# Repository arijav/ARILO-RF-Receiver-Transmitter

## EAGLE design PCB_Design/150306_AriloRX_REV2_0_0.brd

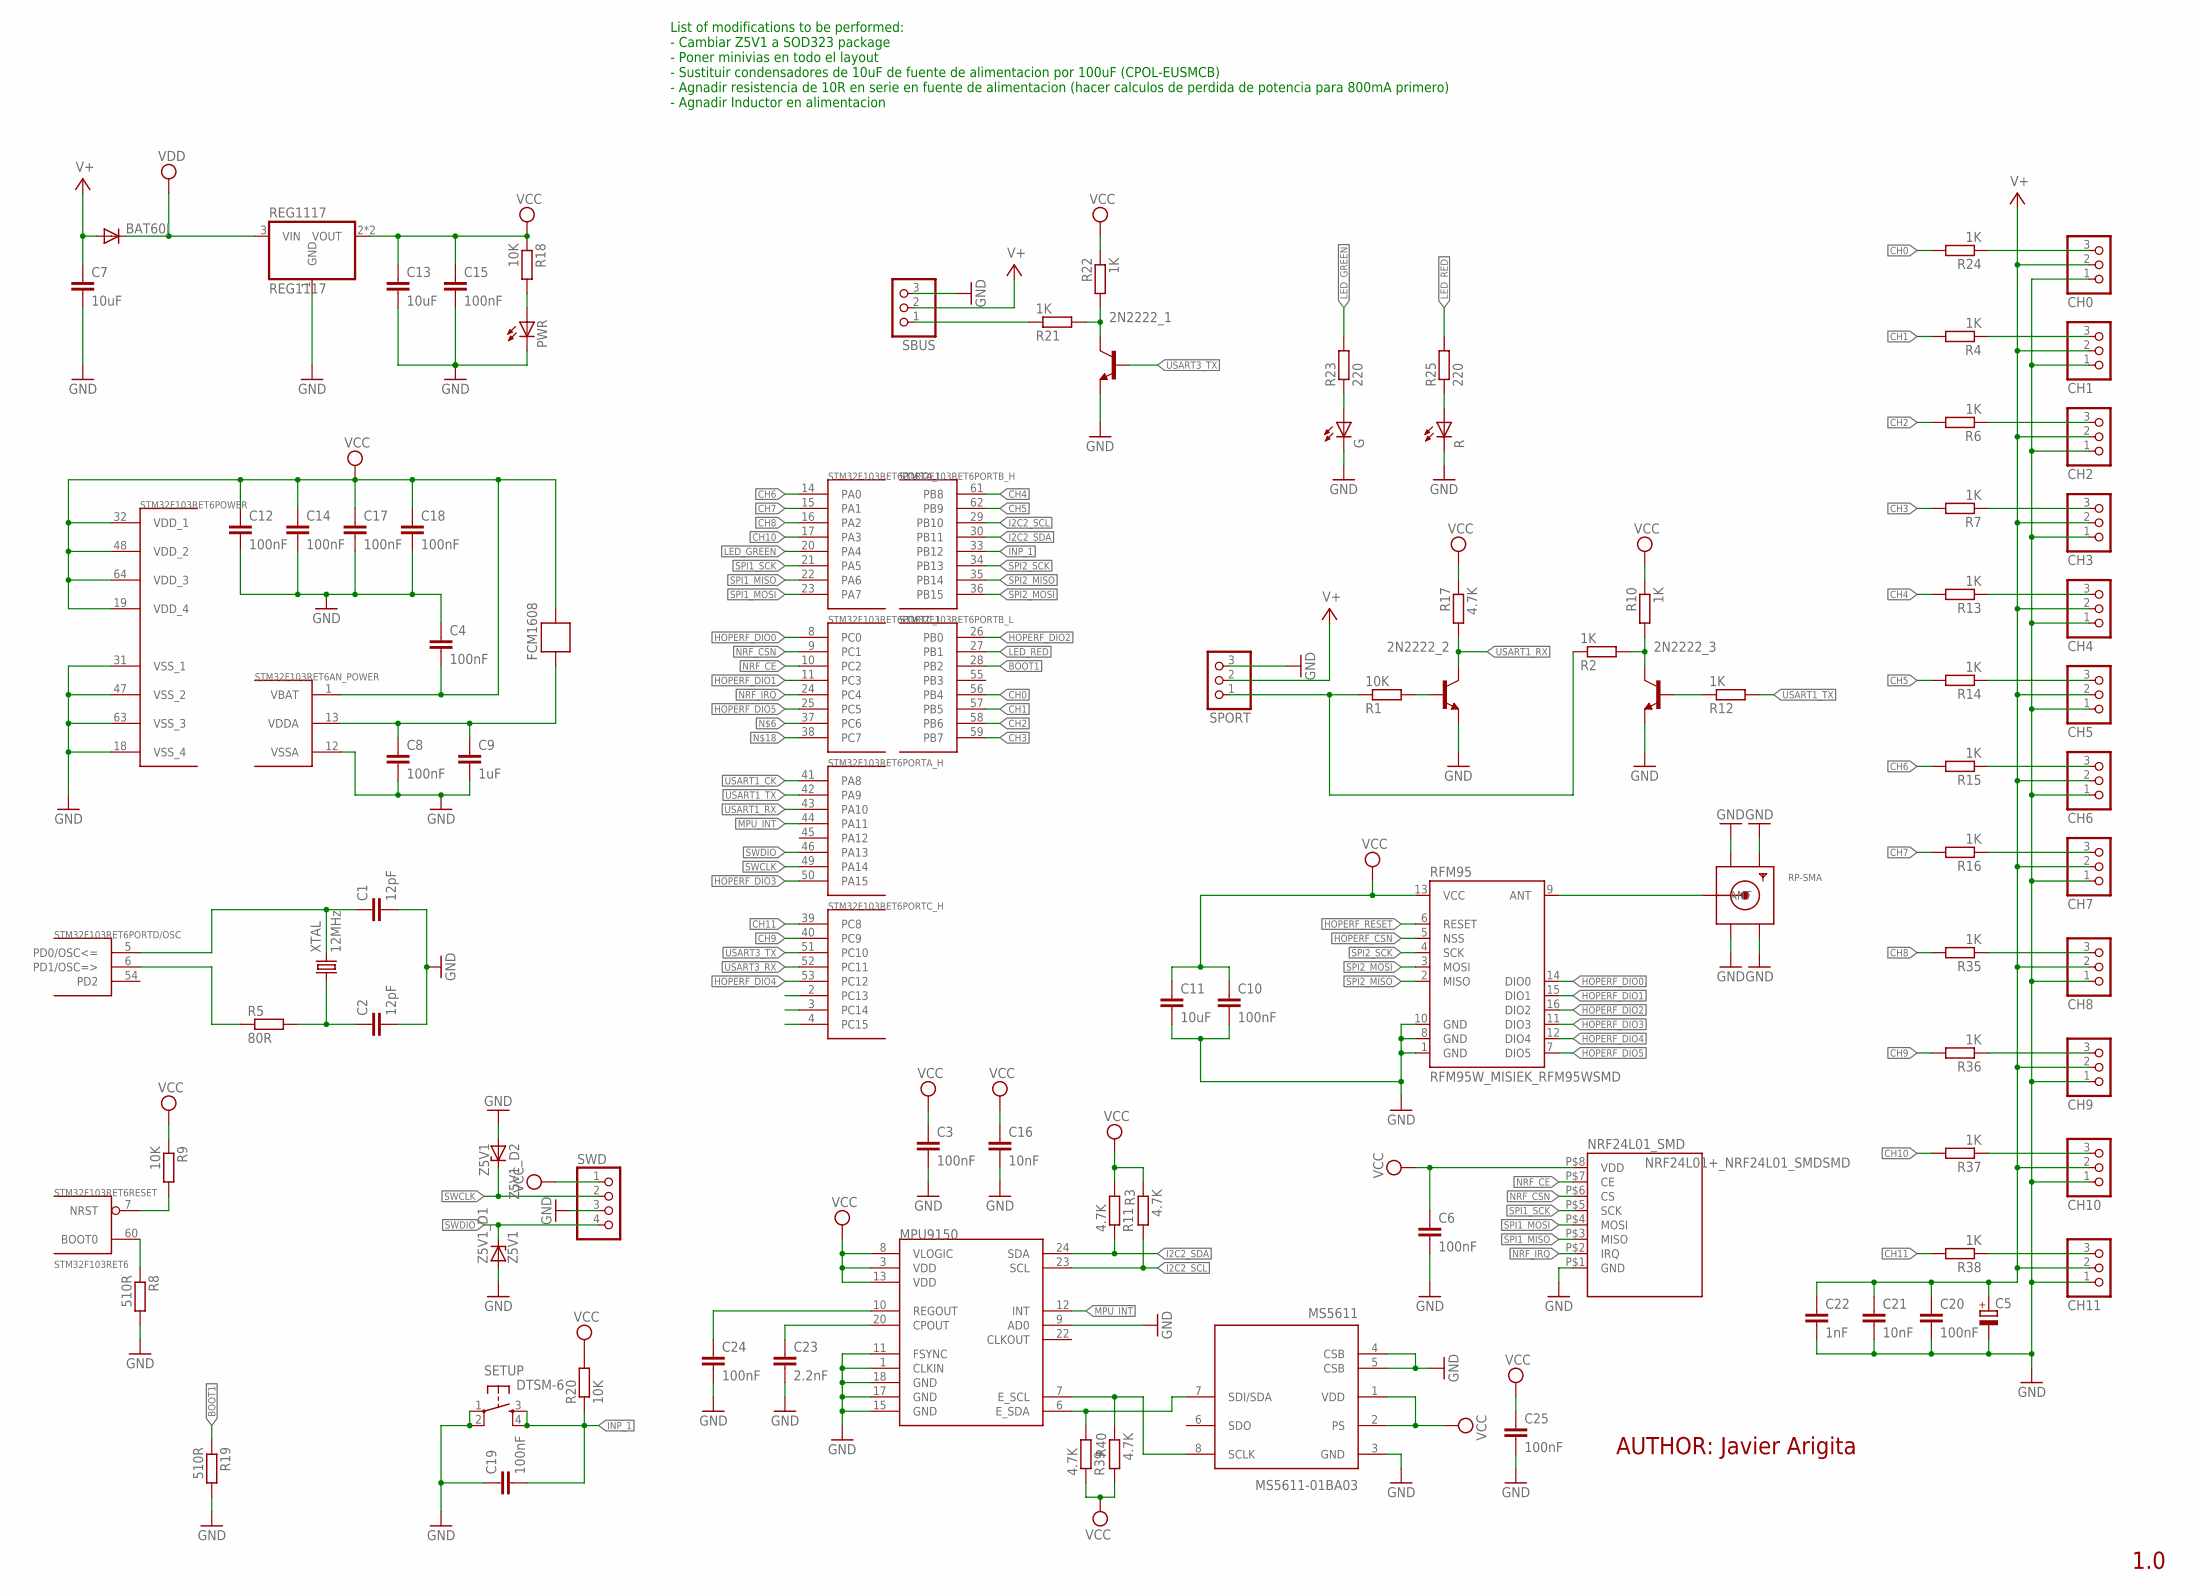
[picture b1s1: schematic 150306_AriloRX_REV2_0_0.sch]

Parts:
2N2222_1, 2N2222_2, 2N2222_3: MMBT2222ALT1-NPN-SOT23-BEC; SOT23-BEC
BAT60J: DIODE-SOD323-R; SOD323-R
C1, C2: 12pF; RESISTOR_C0603
C3, C4, C6, C8, C10, C12, C14, C15, C17, C18, C19, C20, C24, C25: 100nF; RESISTOR_C0603
C5: CPOL-EUSMCB; SMC_B
C7, C11, C13: 10uF; RESISTOR_C3216
C9: 1uF; RESISTOR_C0603
C16, C21: 10nF; RESISTOR_C0603
C22: 1nF; RESISTOR_C0603
C23: 2.2nF; RESISTOR_C0603
CH0, CH1, CH2, CH3, CH4, CH5, CH6, CH7, CH8, CH9, CH10, CH11: PINHD-1X3; 1X03
FCM1608: FERRITE-BEAD; R0603
G: LEDCHIP-LED0603; CHIP-LED0603
MPU9150: MPU-9150QFN-24-NP; QFN-24-NP
MS5611: MS5611-01BA03; SON125P300X500X100-8N
NRF24L01_SMD: NRF24L01+_NRF24L01_SMDSMD; NRF24L01+_NRF24L01_SMD
PWR: LED_LEDCHIP-LED0603; LED_CHIP-LED0603
R: LEDCHIP-LED0603; CHIP-LED0603
R1, R9, R18, R20: 10K; RCL_R0603
R2, R4, R6, R7, R10, R12, R13, R14, R15, R16, R21, R22, R24, R35, R36, R37, R38: 1K; RCL_R0603
R3, R11, R17, R39, R40: 4.7K; RCL_R0603
R5: 80R; RCL_R0603
R8, R19: 510R; RCL_R0603
R23, R25: 220; RCL_R0603
REG1117: REG1117; SOT223
RFM95: RFM95W_MISIEK_RFM95WSMD; RFM95W_MISIEK_RFM95W_SMD
RP-SMA: SMACONNECTOR_EDGE; SMA_EDGELAUNCH
SBUS: PINHD-1X3; 1X03
SETUP: DTSM-6
SPORT: PINHD-1X3; 1X03
STM32F103RET6: STM32F103RET6; TQFP64
SWD: PINHD-1X4; 1X04
XTAL: 12MHz; CRYSTAL-SMD-5X3
Z5V1_D1, Z5V1_D2: Z5V1; SOD80C

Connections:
BOOT1: R19.1, STM32F103RET6.28 (PB2)
CH0: R24.2, STM32F103RET6.56 (PB4)
CH1: R4.2, STM32F103RET6.57 (PB5)
CH2: R6.2, STM32F103RET6.58 (PB6)
CH3: R7.2, STM32F103RET6.59 (PB7)
CH4: R13.2, STM32F103RET6.61 (PB8)
CH5: R14.2, STM32F103RET6.62 (PB9)
CH6: R15.2, STM32F103RET6.14 (PA0)
CH7: R16.2, STM32F103RET6.15 (PA1)
CH8: R35.2, STM32F103RET6.16 (PA2)
CH9: R36.2, STM32F103RET6.40 (PC9)
CH10: R37.2, STM32F103RET6.17 (PA3)
CH11: R38.2, STM32F103RET6.39 (PC8)
GND: 2N2222_1.E, 2N2222_2.E, 2N2222_3.E, C1.2, C2.2, C3.2, C4.1, C5.-, C6.2, C7.2, C8.2, C9.2, C10.2, C11.2, C12.2, C13.2, C14.2, C15.2, C16.2, C17.2, C18.2, C19.1, C20.2, C21.2, C22.2, C23.2, C24.2, C25.2, CH0.1, CH1.1, CH2.1, CH3.1, CH4.1, CH5.1, CH6.1, CH7.1, CH8.1, CH9.1, CH10.1, CH11.1, G.C, MPU9150.1 (CLKIN), MPU9150.9 (AD0), MPU9150.11 (FSYNC), MPU9150.15 (GND), MPU9150.17 (GND), MPU9150.18 (GND), MS5611.3 (GND), MS5611.4 (CSB), MS5611.5 (CSB), NRF24L01_SMD.P$1 (GND), PWR.C, R.C, R8.2, R19.2, REG1117.1 (GND), RFM95.1 (GND), RFM95.8 (GND), RFM95.10 (GND), RP-SMA.GND@1 (GND4), RP-SMA.GND@2 (GND3), RP-SMA.GND@3 (GND2), RP-SMA.GND@4 (GND1), SBUS.3, SETUP.1, SETUP.2, SPORT.3, STM32F103RET6.12 (VSSA), STM32F103RET6.18 (VSS_4), STM32F103RET6.31 (VSS_1), STM32F103RET6.47 (VSS_2), STM32F103RET6.63 (VSS_3), SWD.3, Z5V1_D1.A, Z5V1_D2.A
HOPERF_CSN: RFM95.5 (NSS)
HOPERF_DIO0: RFM95.14 (DIO0), STM32F103RET6.8 (PC0)
HOPERF_DIO1: RFM95.15 (DIO1), STM32F103RET6.11 (PC3)
HOPERF_DIO2: RFM95.16 (DIO2), STM32F103RET6.26 (PB0)
HOPERF_DIO3: RFM95.11 (DIO3), STM32F103RET6.50 (PA15)
HOPERF_DIO4: RFM95.12 (DIO4), STM32F103RET6.53 (PC12)
HOPERF_DIO5: RFM95.7 (DIO5), STM32F103RET6.25 (PC5)
HOPERF_RESET: RFM95.6 (RESET)
I2C2_SCL: MPU9150.23 (SCL), R3.2, STM32F103RET6.29 (PB10)
I2C2_SDA: MPU9150.24 (SDA), R11.1, STM32F103RET6.30 (PB11)
INP_1: C19.2, R20.1, SETUP.3, SETUP.4, STM32F103RET6.33 (PB12)
LED_GREEN: R23.2, STM32F103RET6.20 (PA4)
LED_RED: R25.2, STM32F103RET6.27 (PB1)
MPU_INT: MPU9150.12 (INT), STM32F103RET6.44 (PA11)
unnamed: C1.1, STM32F103RET6.5 (PD0/OSC<=), XTAL.3 (2)
unnamed: R5.1, STM32F103RET6.6 (PD1/OSC=>)
unnamed: C2.1, R5.2, XTAL.1
unnamed: R8.1, STM32F103RET6.60 (BOOT0)
unnamed: 2N2222_3.C, R2.2, R10.2
unnamed: RFM95.9 (ANT), RP-SMA.P (ANT)
unnamed: 2N2222_3.B, R12.1
unnamed: CH0.3, R24.1
unnamed: PWR.A, R18.2
unnamed: 2N2222_1.C, R21.2, R22.2
unnamed: G.A, R23.1
unnamed: CH8.3, R35.1
unnamed: R1.1, R2.1, SPORT.1
unnamed: R.A, R25.1
unnamed: 2N2222_2.B, R1.2
unnamed: C8.1, C9.1, FCM1608.2, STM32F103RET6.13 (VDDA)
unnamed: CH2.3, R6.1
unnamed: CH4.3, R13.1
unnamed: CH9.3, R36.1
unnamed: CH10.3, R37.1
unnamed: CH11.3, R38.1
unnamed: MPU9150.7 (E_SCL), MS5611.8 (SCLK), R40.1
unnamed: MPU9150.6 (E_SDA), MS5611.7 (SDI/SDA), R39.2
unnamed: CH3.3, R7.1
unnamed: CH6.3, R15.1
unnamed: C23.1, MPU9150.20 (CPOUT)
unnamed: CH5.3, R14.1
unnamed: CH7.3, R16.1
unnamed: C24.1, MPU9150.10 (REGOUT)
unnamed: CH1.3, R4.1
NRF_CE: NRF24L01_SMD.P$7 (CE), STM32F103RET6.10 (PC2)
NRF_CSN: NRF24L01_SMD.P$6 (CS), STM32F103RET6.9 (PC1)
NRF_IRQ: NRF24L01_SMD.P$2 (IRQ), STM32F103RET6.24 (PC4)
NSRST: R9.2, STM32F103RET6.7 (NRST)
SBUS: R21.1, SBUS.1
SPI1_MISO: NRF24L01_SMD.P$3 (MISO), STM32F103RET6.22 (PA6)
SPI1_MOSI: NRF24L01_SMD.P$4 (MOSI), STM32F103RET6.23 (PA7)
SPI1_SCK: NRF24L01_SMD.P$5 (SCK), STM32F103RET6.21 (PA5)
SPI2_MISO: RFM95.2 (MISO), STM32F103RET6.35 (PB14)
SPI2_MOSI: RFM95.3 (MOSI), STM32F103RET6.36 (PB15)
SPI2_SCK: RFM95.4 (SCK), STM32F103RET6.34 (PB13)
SWCLK: STM32F103RET6.49 (PA14), SWD.2, Z5V1_D2.C
SWDIO: STM32F103RET6.46 (PA13), SWD.4, Z5V1_D1.C
USART1_CK: STM32F103RET6.41 (PA8)
USART1_RX: 2N2222_2.C, R17.2, STM32F103RET6.43 (PA10)
USART1_TX: R12.2, STM32F103RET6.42 (PA9)
USART3_RX: STM32F103RET6.52 (PC11)
USART3_TX: 2N2222_1.B, STM32F103RET6.51 (PC10)
V+: BAT60J.A, C5.+, C7.1, C20.1, C21.1, C22.1, CH0.2, CH1.2, CH2.2, CH3.2, CH4.2, CH5.2, CH6.2, CH7.2, CH8.2, CH9.2, CH10.2, CH11.2, SBUS.2, SPORT.2
VCC: C3.1, C4.2, C6.1, C10.1, C11.1, C12.1, C13.1, C14.1, C15.1, C16.1, C17.1, C18.1, C25.1, FCM1608.1, MPU9150.3 (VDD), MPU9150.8 (VLOGIC), MPU9150.13 (VDD), MS5611.1 (VDD), MS5611.2 (PS), NRF24L01_SMD.P$8 (VDD), R3.1, R9.1, R10.1, R11.2, R17.1, R18.1, R20.2, R22.1, R39.1, R40.2, REG1117.2 (VOUT), REG1117.4 (VOUT), RFM95.13 (VCC), STM32F103RET6.1 (VBAT), STM32F103RET6.19 (VDD_4), STM32F103RET6.32 (VDD_1), STM32F103RET6.48 (VDD_2), STM32F103RET6.64 (VDD_3), SWD.1
VDD: BAT60J.C, REG1117.3 (VIN)

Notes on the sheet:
AUTHOR: Javier Arigita
1.0
List of modifications to be performed: - Cambiar Z5V1 a SOD323 package - Poner minivias en todo el layout - Sustituir condensadores de 10uF de fuente de alimentacion por 100uF (CPOL-EUSMCB) - Agnadir resistencia de 10R en serie en fuente de alimentacion (hacer calculos de perdida de potencia para 8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

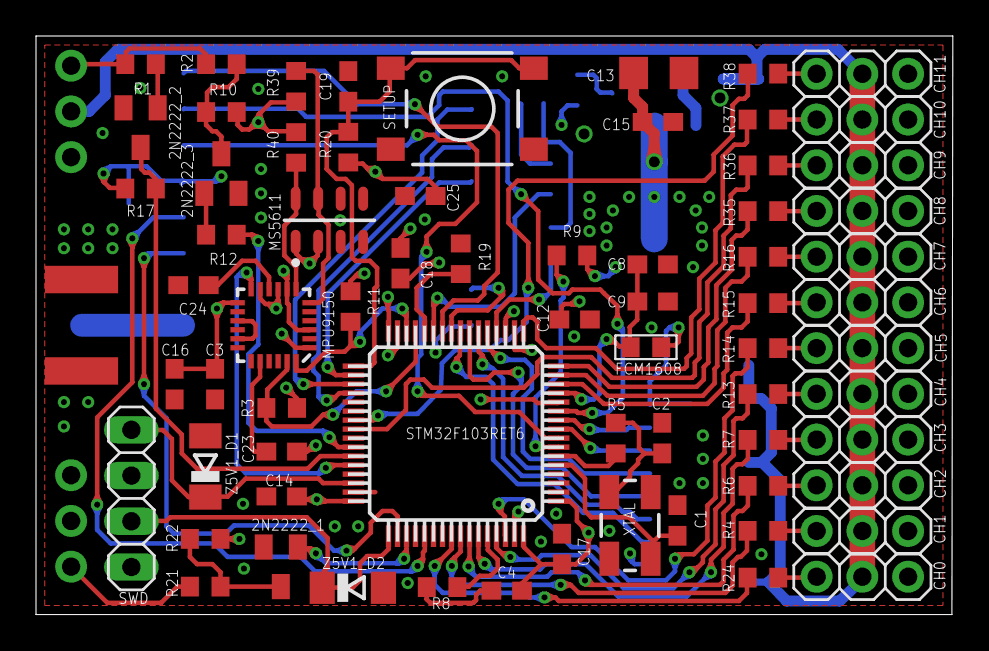
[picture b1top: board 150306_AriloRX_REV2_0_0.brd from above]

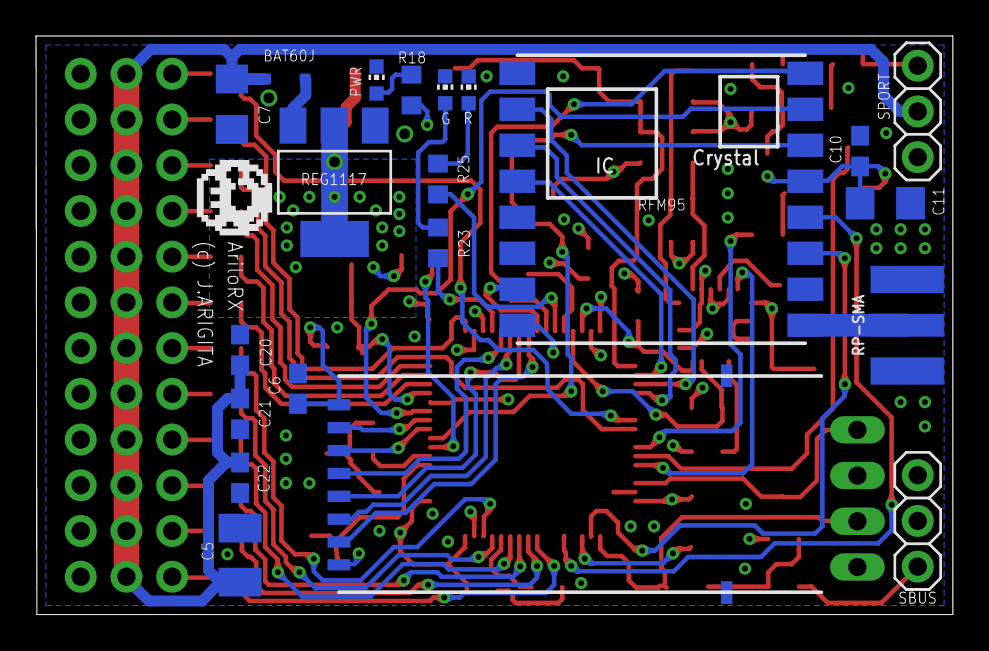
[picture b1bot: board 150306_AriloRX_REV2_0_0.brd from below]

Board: 4 copper layers, 50.9 x 32.1 mm, 90 parts (21 on the bottom side), 75 nets.

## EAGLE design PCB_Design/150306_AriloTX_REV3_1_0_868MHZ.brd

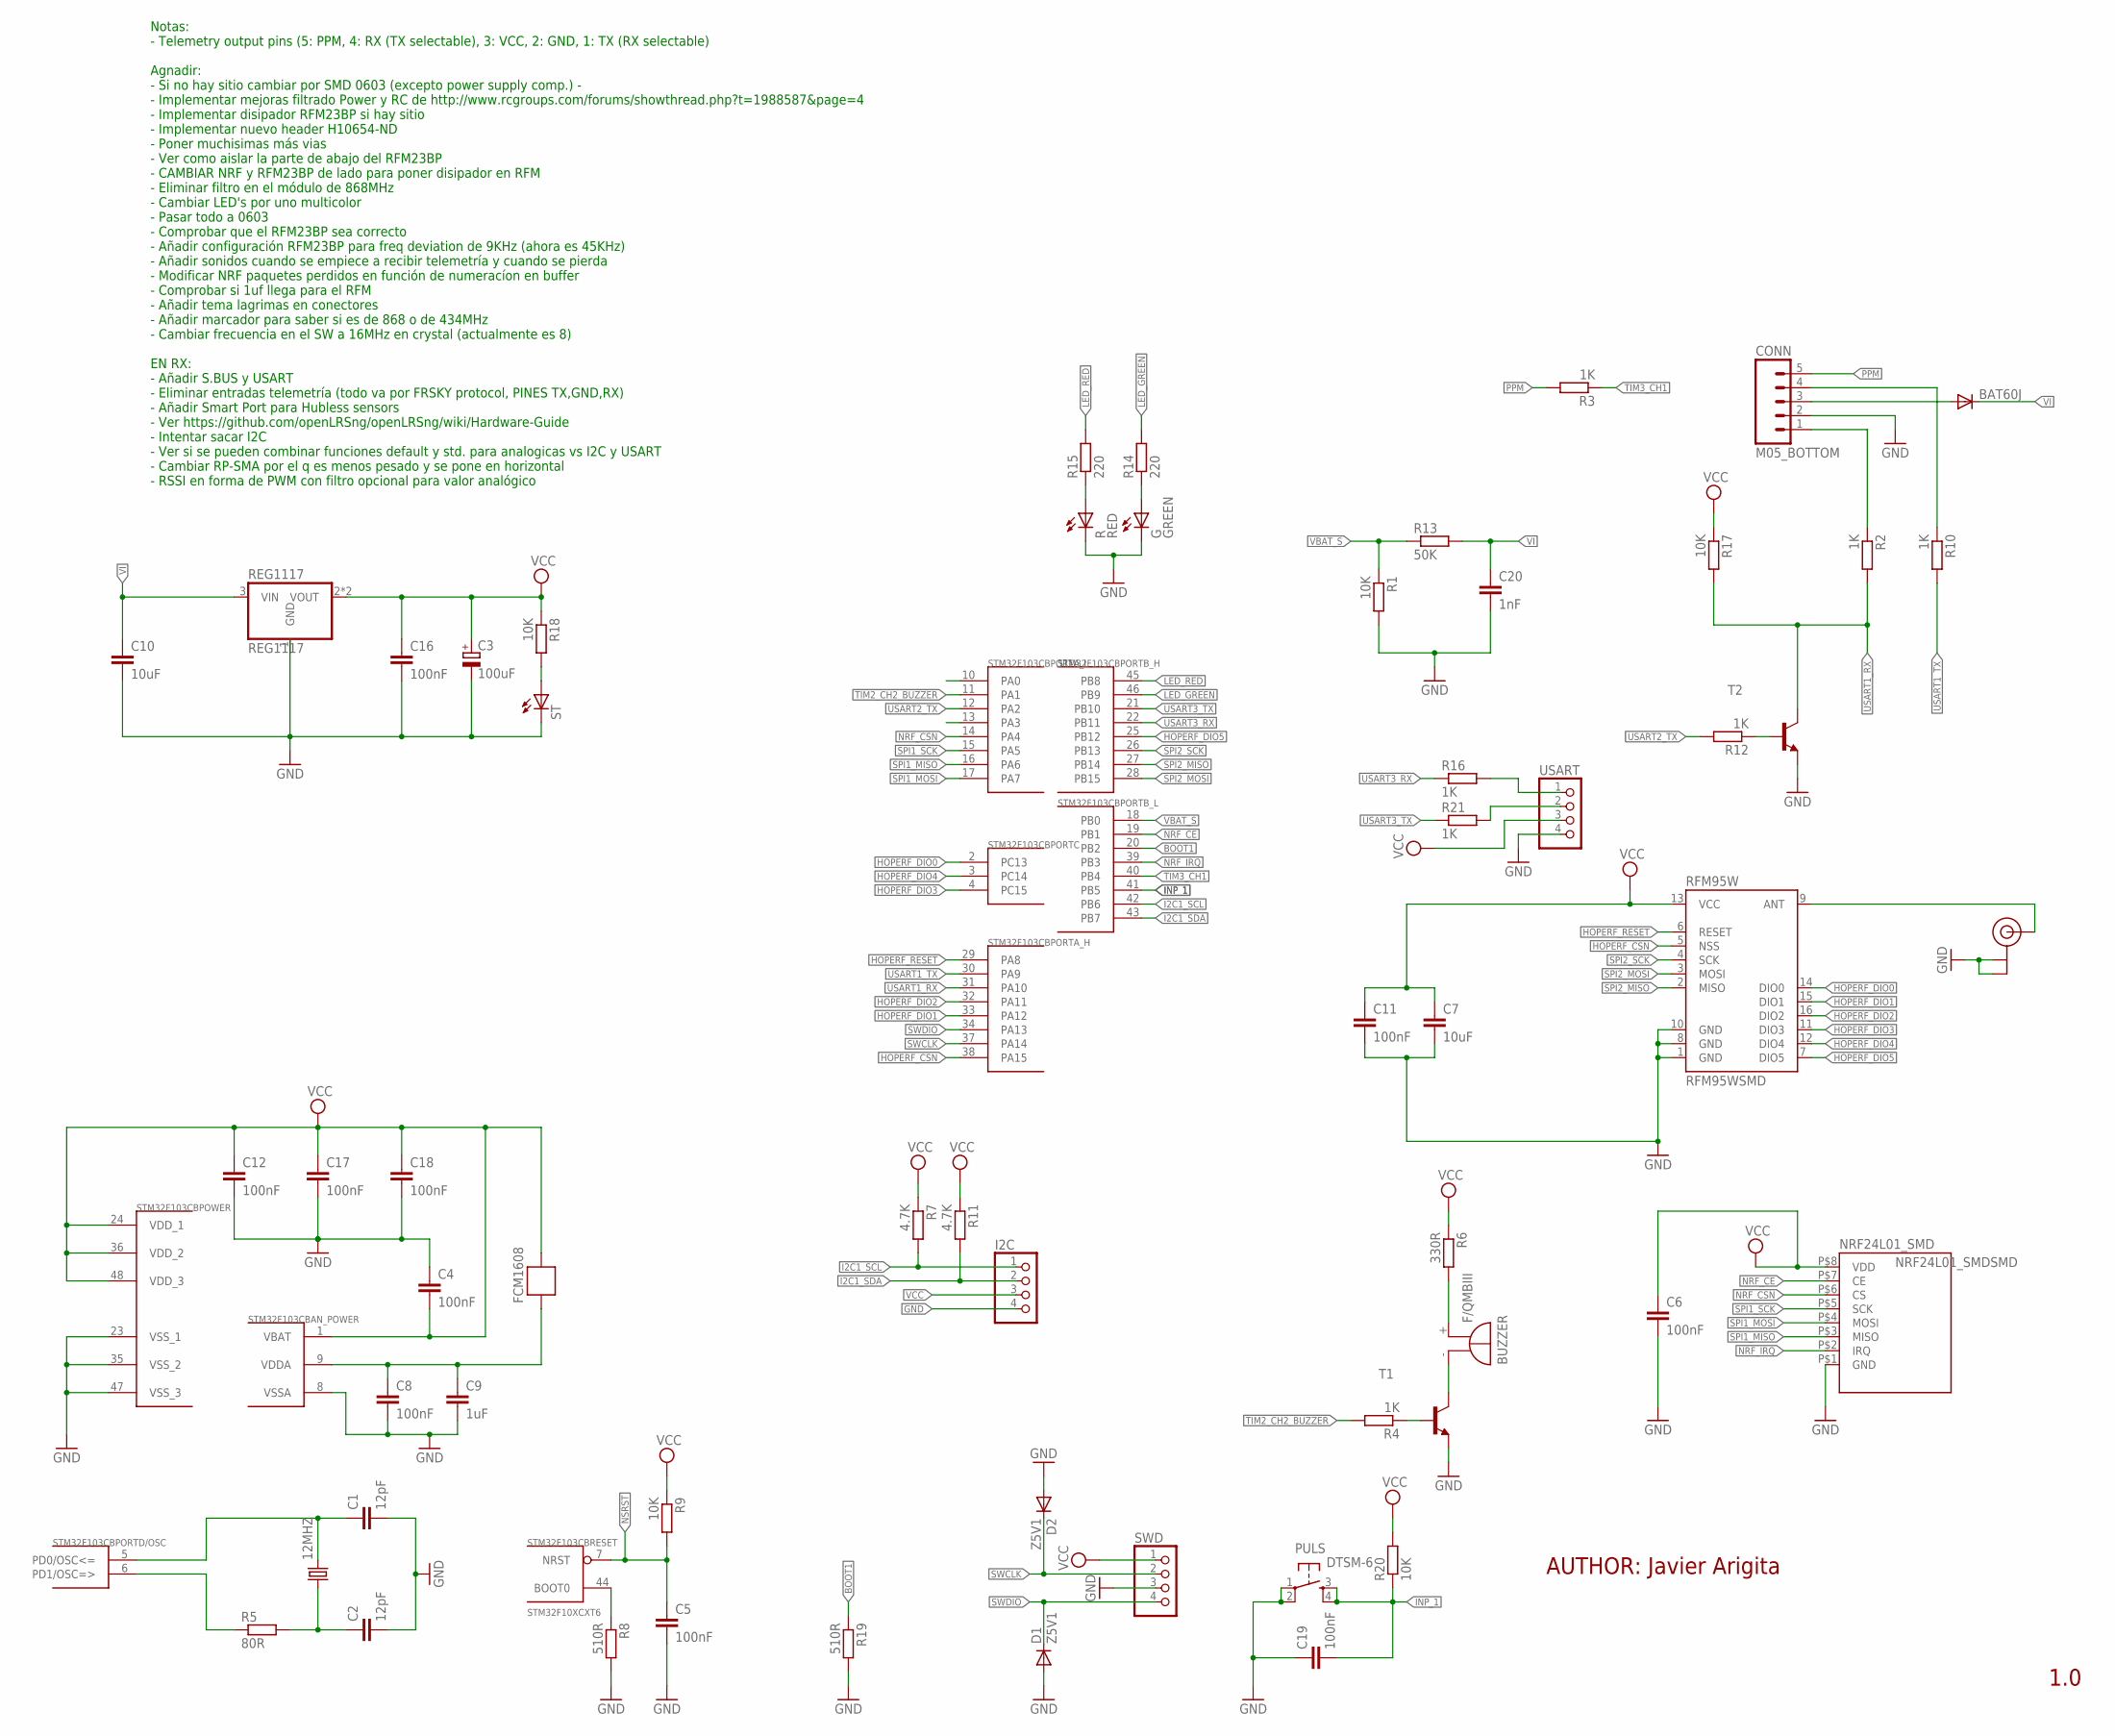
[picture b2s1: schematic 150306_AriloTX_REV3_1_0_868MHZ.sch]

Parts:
12MHZ: CRYSTAL5X3; CRYSTAL-SMD-5X3
BAT60J: DIODE-SOD323-R; SOD323-R
BUZZER: F/QMBIII
C1, C2: 12pF; C0603
C3: 100uF; SMC_B
C4, C5, C6, C8, C11, C12, C16, C17, C18, C19: 100nF; C0603
C7, C10: 10uF; C3216
C9: 1uF; C0603
C20: 1nF; C0603
CONN: M05_BOTTOM
D1, D2: Z5V1; SOD323-R
FCM1608: FERRITE-BEAD; R0603
G: GREEN; CHIP-LED0603
I2C: PINHD-1X4; 1X04
NRF24L01_SMD: NRF24L01_SMDSMD; NRF24L01_SMD
PULS: DTSM-6
R: RED; CHIP-LED0603
R1, R9, R17, R18, R20: 10K; R0603
R2, R3, R4, R10, R12, R16, R21: 1K; R0603
R5: 80R; R0603
R6: 330R; R0603
R7, R11: 4.7K; R0603
R8, R19: 510R; R0603
R13: 50K; R0603
R14, R15: 220; R0603
REG1117: REG1117; SOT223
RFM95W: RFM95WSMD; MISIEK_RFM95W_SMD
ST: LEDCHIP-LED0603; CHIP-LED0603
STM32F103CB: STM32F10XCXT6; TQFP48
SWD: PINHD-1X4; 1X04
T1, T2: BC848-NPN-SOT23-BEC; SOT23-BEC
U.FL: U.FL
USART: PINHD-1X4; 1X04

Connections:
BOOT1: R19.1, STM32F103CB.20 (PB2)
GND: C1.2, C2.2, C3.-, C4.1, C5.2, C6.2, C7.2, C8.2, C9.2, C10.2, C11.2, C12.2, C16.2, C17.2, C18.2, C19.1, C20.2, CONN.2, D1.A, D2.A, G.C, I2C.4, NRF24L01_SMD.P$1 (GND), PULS.1, PULS.2, R.C, R1.2, R8.2, R19.2, REG1117.1 (GND), RFM95W.1 (GND), RFM95W.8 (GND), RFM95W.10 (GND), ST.C, STM32F103CB.8 (VSSA), STM32F103CB.23 (VSS_1), STM32F103CB.35 (VSS_2), STM32F103CB.47 (VSS_3), SWD.3, T1.E, T2.E, U.FL.P$1 (GND), U.FL.P$2 (GND), USART.4
HOPERF_CSN: RFM95W.5 (NSS), STM32F103CB.38 (PA15)
HOPERF_DIO0: RFM95W.14 (DIO0), STM32F103CB.2 (PC13)
HOPERF_DIO1: RFM95W.15 (DIO1), STM32F103CB.33 (PA12)
HOPERF_DIO2: RFM95W.16 (DIO2), STM32F103CB.32 (PA11)
HOPERF_DIO3: RFM95W.11 (DIO3), STM32F103CB.4 (PC15)
HOPERF_DIO4: RFM95W.12 (DIO4), STM32F103CB.3 (PC14)
HOPERF_DIO5: RFM95W.7 (DIO5), STM32F103CB.25 (PB12)
HOPERF_RESET: RFM95W.6 (RESET), STM32F103CB.29 (PA8)
I2C1_SCL: I2C.1, R7.2, STM32F103CB.42 (PB6)
I2C1_SDA: I2C.2, R11.2, STM32F103CB.43 (PB7)
INP_1: C19.2, PULS.3, PULS.4, R20.1, STM32F103CB.41 (PB5)
LED_GREEN: R14.2, STM32F103CB.46 (PB9)
LED_RED: R15.2, STM32F103CB.45 (PB8)
unnamed: 12MHZ.3 (2), C1.1, STM32F103CB.5 (PD0/OSC<=)
unnamed: R5.1, STM32F103CB.6 (PD1/OSC=>)
unnamed: 12MHZ.1, C2.1, R5.2
unnamed: R8.1, STM32F103CB.44 (BOOT0)
unnamed: R12.1, T2.B
unnamed: CONN.1, R2.1
unnamed: R.A, R15.1
unnamed: G.A, R14.1
unnamed: CONN.4, R10.1
unnamed: R18.2, ST.A
unnamed: RFM95W.9 (ANT), U.FL.P$3 (SIGNAL)
unnamed: R16.2, USART.1
unnamed: R21.2, USART.2
unnamed: BAT60J.A, CONN.3
unnamed: BUZZER.+ (-), R6.2
unnamed: C8.1, C9.1, FCM1608.2, STM32F103CB.9 (VDDA)
unnamed: R4.1, T1.B
unnamed: BUZZER.- (+), T1.C
NRF_CE: NRF24L01_SMD.P$7 (CE), STM32F103CB.19 (PB1)
NRF_CSN: NRF24L01_SMD.P$6 (CS), STM32F103CB.14 (PA4)
NRF_IRQ: NRF24L01_SMD.P$2 (IRQ), STM32F103CB.39 (PB3)
NSRST: C5.1, R9.2, STM32F103CB.7 (NRST)
PPM: CONN.5, R3.2
SPI1_MISO: NRF24L01_SMD.P$3 (MISO), STM32F103CB.16 (PA6)
SPI1_MOSI: NRF24L01_SMD.P$4 (MOSI), STM32F103CB.17 (PA7)
SPI1_SCK: NRF24L01_SMD.P$5 (SCK), STM32F103CB.15 (PA5)
SPI2_MISO: RFM95W.2 (MISO), STM32F103CB.27 (PB14)
SPI2_MOSI: RFM95W.3 (MOSI), STM32F103CB.28 (PB15)
SPI2_SCK: RFM95W.4 (SCK), STM32F103CB.26 (PB13)
SWCLK: D2.C, STM32F103CB.37 (PA14), SWD.2
SWDIO: D1.C, STM32F103CB.34 (PA13), SWD.4
TIM2_CH2_BUZZER: R4.2, STM32F103CB.11 (PA1)
TIM3_CH1: R3.1, STM32F103CB.40 (PB4)
USART1_RX: R2.2, R17.2, STM32F103CB.31 (PA10), T2.C
USART1_TX: R10.2, STM32F103CB.30 (PA9)
USART2_TX: R12.2, STM32F103CB.12 (PA2)
USART3_RX: R16.1, STM32F103CB.22 (PB11)
USART3_TX: R21.1, STM32F103CB.21 (PB10)
VBAT_S: R1.1, R13.1, STM32F103CB.18 (PB0)
VCC: C3.+, C4.2, C6.1, C7.1, C11.1, C12.1, C16.1, C17.1, C18.1, FCM1608.1, I2C.3, NRF24L01_SMD.P$8 (VDD), R6.1, R7.1, R9.1, R11.1, R17.1, R18.1, R20.2, REG1117.2 (VOUT), REG1117.4 (VOUT), RFM95W.13 (VCC), STM32F103CB.1 (VBAT), STM32F103CB.24 (VDD_1), STM32F103CB.36 (VDD_2), STM32F103CB.48 (VDD_3), SWD.1, USART.3
VI: BAT60J.C, C10.1, C20.1, R13.2, REG1117.3 (VIN)

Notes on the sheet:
AUTHOR: Javier Arigita
1.0
Notas: - Telemetry output pins (5: PPM, 4: RX (TX selectable), 3: VCC, 2: GND, 1: TX (RX selectable) Agnadir: - Si no hay sitio cambiar por SMD 0603 (excepto power supply comp.) - - Implementar mejoras filtrado Power y RC de http://www.rcgroups.com/forums/showthread.php?t=1988587&page=4 - Implement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

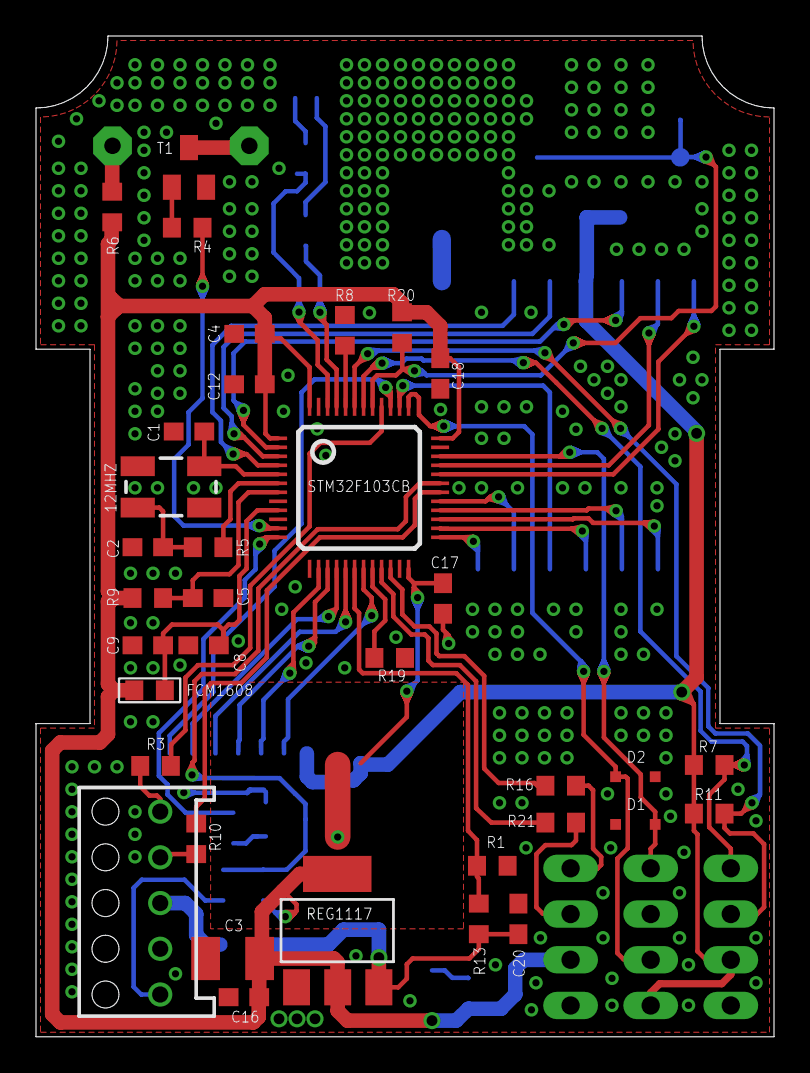
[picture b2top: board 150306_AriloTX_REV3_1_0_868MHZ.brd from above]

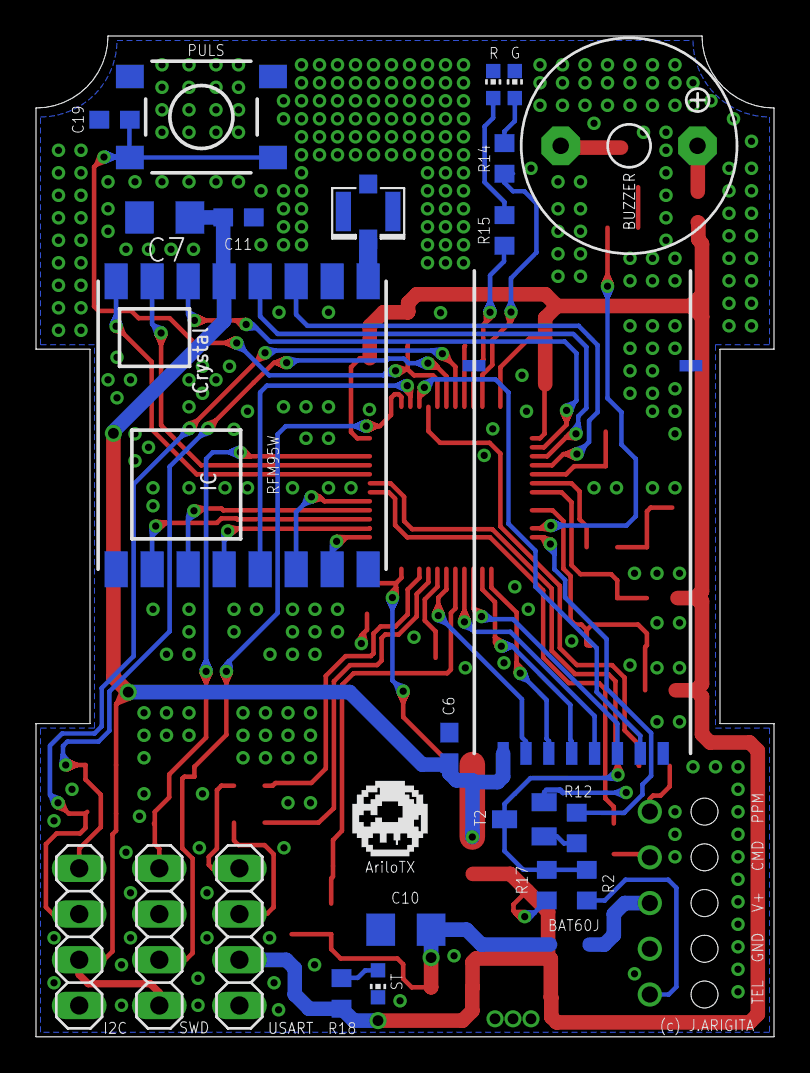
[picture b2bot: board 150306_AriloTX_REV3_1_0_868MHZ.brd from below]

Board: 2 copper layers, 41.0 x 55.6 mm, 59 parts (24 on the bottom side), 56 nets.

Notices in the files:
parts and their libraries:
SparkFun-Sensors: Licensing: CC v3.0 Share-Alike You are welcome to use this library for commercial purposes.
